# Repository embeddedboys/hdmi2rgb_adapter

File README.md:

HDMI2RGB Adapter
----------------

hdmi2rgb_adapter is a simple HDMI to RGB deserializer based on TFP401 (TI) 

FAQS
----

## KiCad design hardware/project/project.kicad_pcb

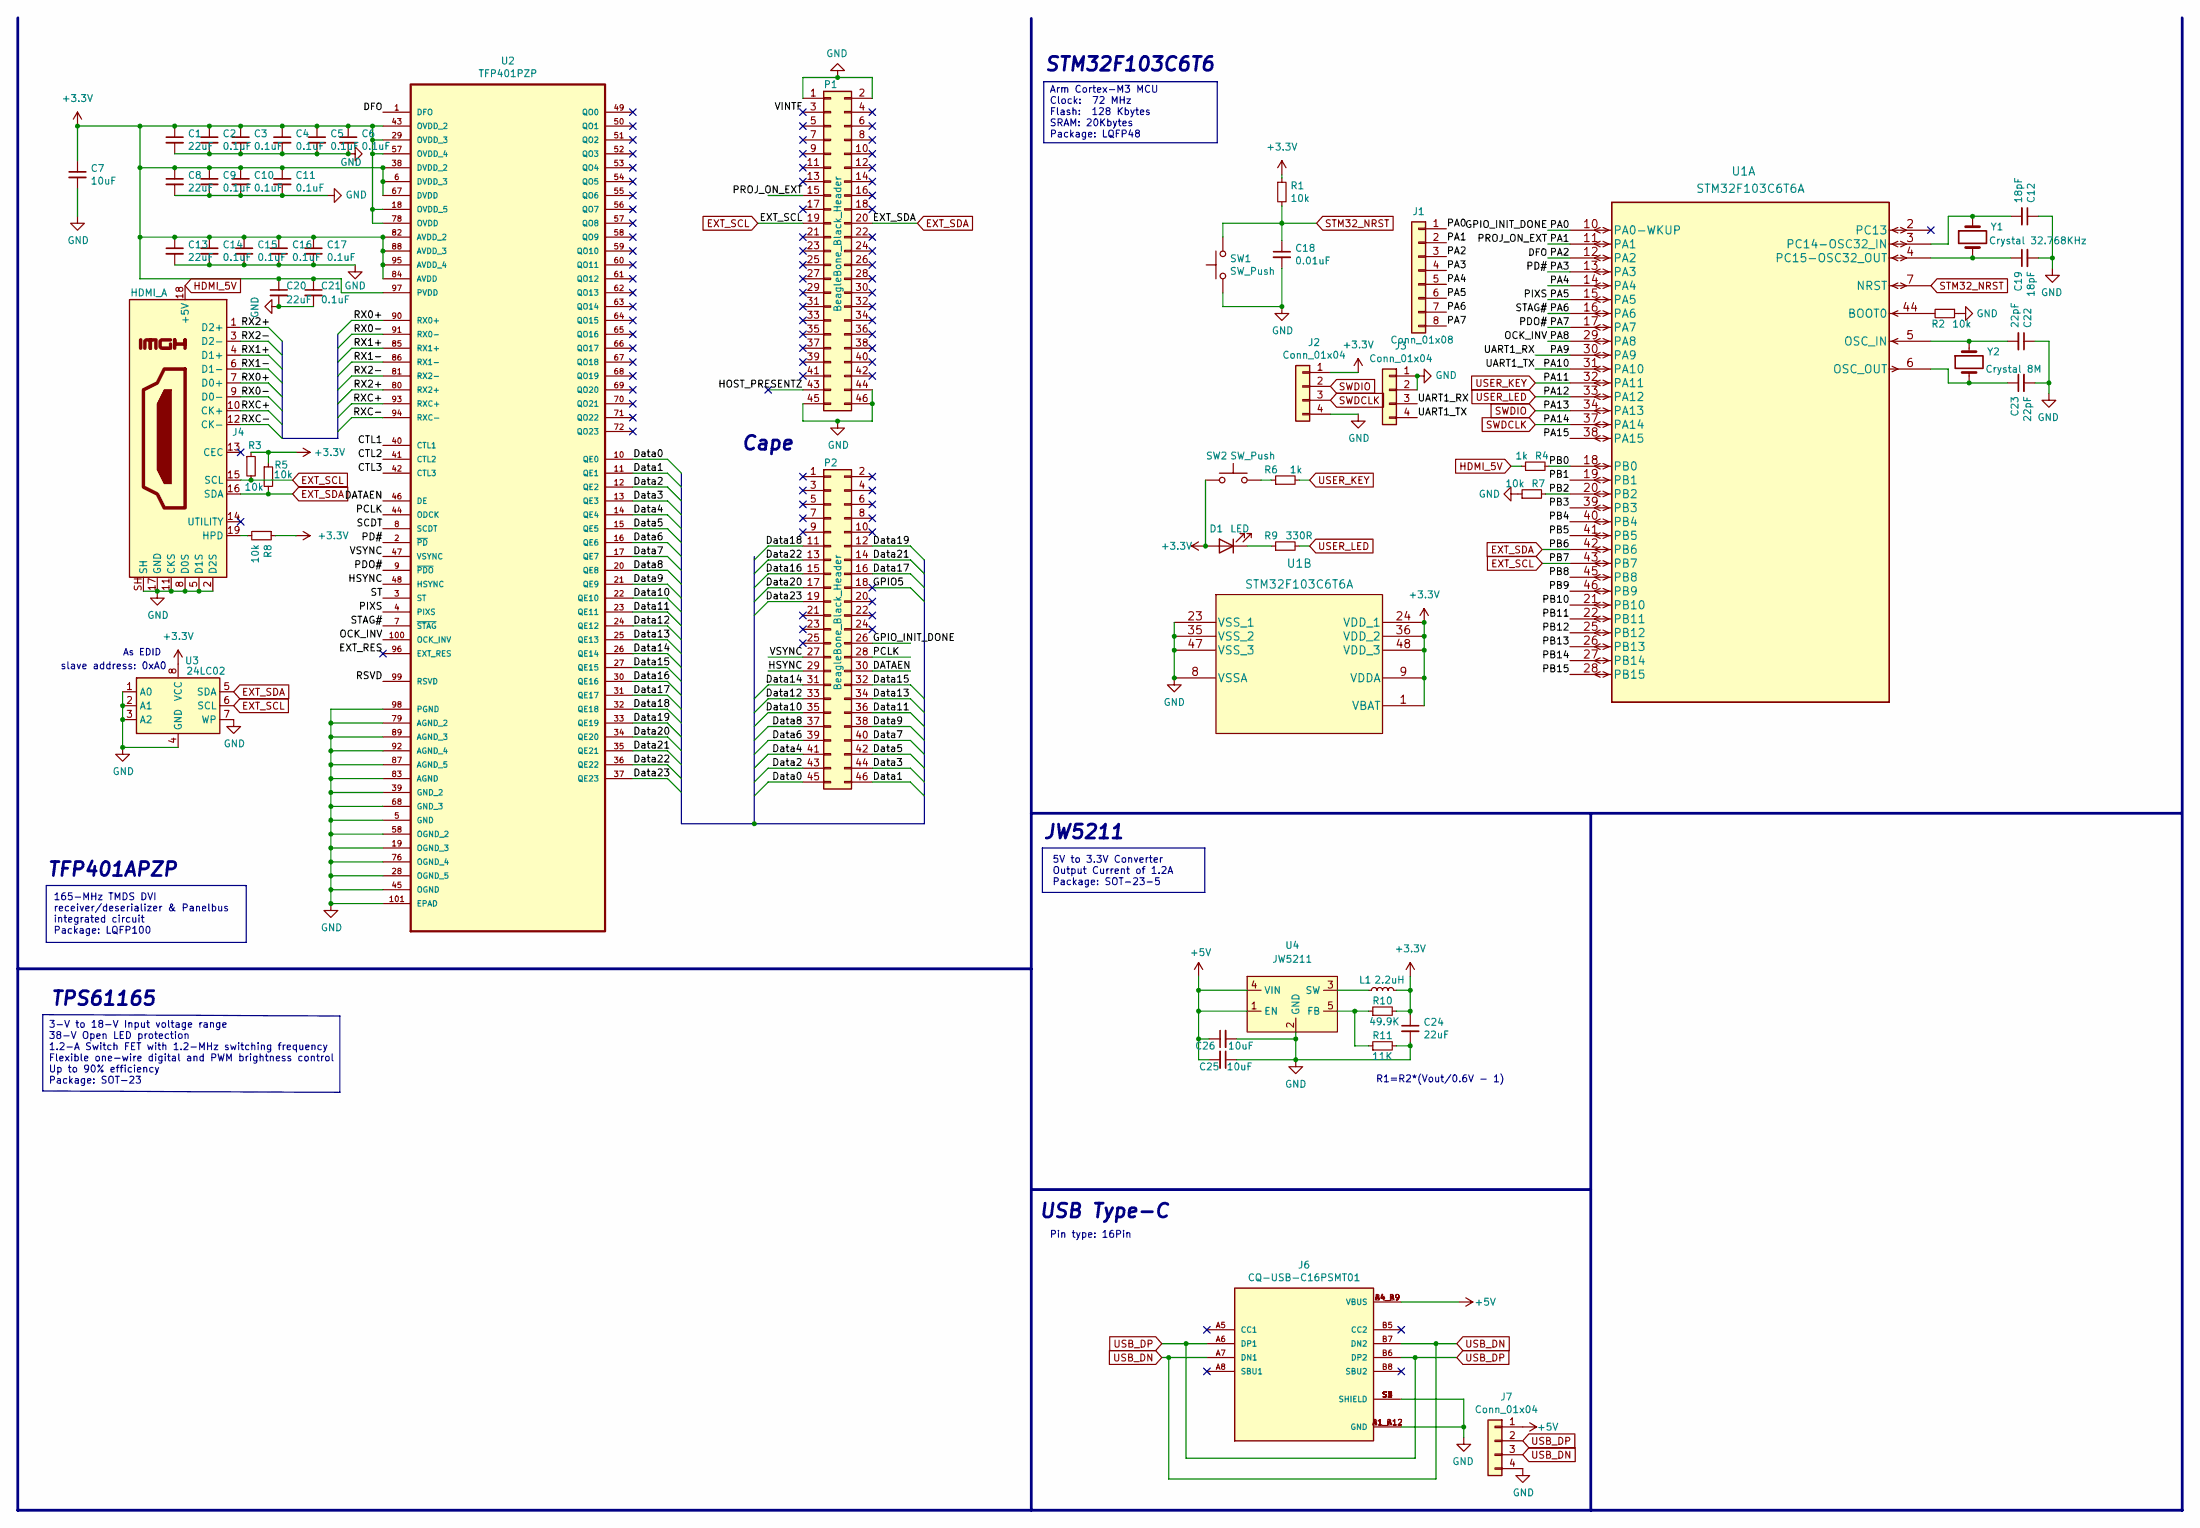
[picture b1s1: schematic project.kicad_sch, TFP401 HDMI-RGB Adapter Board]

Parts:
C1, C8, C13, C20, C24: 22uF; C_0805_2012Metric
C2, C3, C4, C5, C6, C9, C10, C11, C14, C15, C16, C17, C21: 0.1uF; C_0805_2012Metric
C7, C25, C26: 10uF; C_0805_2012Metric
C12, C19: 18pF; C_0805_2012Metric
C18: 0.01uF; C_0805_2012Metric
C22, C23: 22pF; C_0805_2012Metric
D1: LED; LED_0805_2012Metric
J1: Conn_01x08; PinHeader_1x08_P2.54mm_Vertical
J2, J3, J7: Conn_01x04; PinHeader_1x04_P2.54mm_Vertical
J4: HDMI_A; TE_1827059-3
J6: CQ-USB-C16PSMT01; SHENZHEN-CHUANGQIN-TECHNOLOGY_CQ-USB-C16PSMT01; PARTREV A
L1: 2.2uH; L_7.3x7.3_H4.5
P1, P2: BeagleBone_Black_Header; Socket_BeagleBone_Black
R1, R2, R3, R5, R7, R8: 10k; R_0805_2012Metric
R4, R6: 1k; R_0805_2012Metric
R9: 330R; R_0805_2012Metric
R10: 49.9K; R_0805_2012Metric
R11: 11K; R_0805_2012Metric
SW1, SW2: SW_Push; SW_SPST_CK_KXT3
U1: STM32F103C6T6A
U2: TFP401PZP; QFP50P1600X1600X120-101N; MPN TFP401PZP
U3: 24LC02; SOIC-8-1EP_3.9x4.9mm_P1.27mm_EP2.29x3mm
U4: JW5211; SOT-23-5
Y1: Crystal 32.768KHz; Crystal_SMD_3215-2Pin_3.2x1.5mm
Y2: Crystal 8M; Crystal_SMD_5032-2Pin_5.0x3.2mm

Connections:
+3V3: C1.1, C2.1, C3.1, C4.1, C5.1, C6.1, C7.1, C8.1, C9.1, C10.1, C11.1, C13.1, C14.1, C15.1, C16.1, C17.1, C20.1, C21.1, C24.1, D1.2 (A), J2.1, L1.2, R1.1, R3.1, R5.1, R8.1, R10.2, SW2.1, U1.1 (VBAT), U1.9 (VDDA), U1.24 (VDD_1), U1.36 (VDD_2), U1.48 (VDD_3), U2.6 (DVDD_3), U2.18 (OVDD_5), U2.29 (OVDD_3), U2.38 (DVDD_2), U2.43 (OVDD_2), U2.57 (OVDD_4), U2.67 (DVDD), U2.78 (OVDD), U2.82 (AVDD_2), U2.84 (AVDD), U2.88 (AVDD_3), U2.95 (AVDD_4), U2.97 (PVDD), U3.8 (VCC)
+5V: C25.2, C26.1, J6.A4_B9 (VBUS), J6.B4_A9 (VBUS), J7.1, U4.1 (EN), U4.4 (VIN)
/CTL1: U2.40 (CTL1)
/CTL2: U2.41 (CTL2)
/CTL3: U2.42 (CTL3)
/DATAEN: P2.30, U2.46 (DE)
/DFO: J1.3, U1.12 (PA2), U2.1 (DFO)
/Data0: P2.45, U2.10 (QE0)
/Data1: P2.46, U2.11 (QE1)
/Data2: P2.43, U2.12 (QE2)
/Data3: P2.44, U2.13 (QE3)
/Data4: P2.41, U2.14 (QE4)
/Data5: P2.42, U2.15 (QE5)
/Data6: P2.39, U2.16 (QE6)
/Data7: P2.40, U2.17 (QE7)
/Data8: P2.37, U2.20 (QE8)
/Data9: P2.38, U2.21 (QE9)
/Data10: P2.35, U2.22 (QE10)
/Data11: P2.36, U2.23 (QE11)
/Data12: P2.33, U2.24 (QE12)
/Data13: P2.34, U2.25 (QE13)
/Data14: P2.31, U2.26 (QE14)
/Data15: P2.32, U2.27 (QE15)
/Data16: P2.15, U2.30 (QE16)
/Data17: P2.16, U2.31 (QE17)
/Data18: P2.11, U2.32 (QE18)
/Data19: P2.12, U2.33 (QE19)
/Data20: P2.17, U2.34 (QE20)
/Data21: P2.14, U2.35 (QE21)
/Data22: P2.13, U2.36 (QE22)
/Data23: P2.19, U2.37 (QE23)
/EXT_RES: U2.96 (EXT_RES)
/GPIO5: P2.18
/GPIO_INIT_DONE: J1.1, P2.26, U1.10 (PA0-WKUP)
/HOST_PRESENTZ: P1.43
/HSYNC: P2.29, U2.48 (HSYNC)
/OCK_INV: U1.29 (PA8), U2.100 (OCK_INV)
/PA1: J1.2, P1.15, U1.11 (PA1)
/PA3: J1.4, U1.13 (PA3), U2.2 (~PD)
/PA4: J1.5, U1.14 (PA4)
/PA5: J1.6, U1.15 (PA5), U2.4 (PIXS)
/PA6: J1.7, U1.16 (PA6), U2.7 (~STAG)
/PA7: J1.8, U1.17 (PA7), U2.9 (~PDO)
/PA9: J3.3, U1.30 (PA9)
/PA10: J3.4, U1.31 (PA10)
/PA15: U1.38 (PA15)
/PB0: R4.2, U1.18 (PB0)
/PB1: U1.19 (PB1)
/PB2: R7.2, U1.20 (PB2)
/PB3: U1.39 (PB3)
/PB4: U1.40 (PB4)
/PB5: U1.41 (PB5)
/PB8: U1.45 (PB8)
/PB9: U1.46 (PB9)
/PB10: U1.21 (PB10)
/PB11: U1.22 (PB11)
/PB12: U1.25 (PB12)
/PB13: U1.26 (PB13)
/PB14: U1.27 (PB14)
/PB15: U1.28 (PB15)
/PCLK: P2.28, U2.44 (ODCK)
/RSVD: U2.99 (RSVD)
/RX0+: J4.7 (D0+), U2.90 (RX0+)
/RX0-: J4.9 (D0-), U2.91 (RX0-)
/RX1+: J4.4 (D1+), U2.85 (RX1+)
/RX1-: J4.6 (D1-), U2.86 (RX1-)
/RX2+: J4.1 (D2+), U2.80 (RX2+)
/RX2-: J4.3 (D2-), U2.81 (RX2-)
/RXC+: J4.10 (CK+), U2.93 (RXC+)
/RXC-: J4.12 (CK-), U2.94 (RXC-)
/SCDT: U2.8 (SCDT)
/ST: U2.3 (ST)
/VINTF: P1.3
/VSYNC: P2.27, U2.47 (VSYNC)
EXT_SCL: J4.15 (SCL), P1.19, R3.2, U1.43 (PB7), U3.6 (SCL)
EXT_SDA: J4.16 (SDA), P1.20, R5.2, U1.42 (PB6), U3.5 (SDA)
GND: C1.2, C2.2, C3.2, C4.2, C5.2, C6.2, C7.2, C8.2, C9.2, C10.2, C11.2, C12.1, C13.2, C14.2, C15.2, C16.2, C17.2, C18.2, C19.2, C20.2, C21.2, C22.1, C23.2, C24.2, C25.1, C26.2, J2.4, J3.1, J3.2, J4.2 (D2S), J4.5 (D1S), J4.8 (D0S), J4.11 (CKS), J4.17 (GND), J4.SH, J6.A1_B12 (GND), J6.B1_A12 (GND), J6.S1 (SHIELD), J6.S2 (SHIELD), J6.S3 (SHIELD), J6.S4 (SHIELD), J7.4, P1.1, P1.2, P1.44, P1.45, P1.46, R2.1, R7.1, R11.2, SW1.1, U1.8 (VSSA), U1.23 (VSS_1), U1.35 (VSS_2), U1.47 (VSS_3), U2.5 (GND), U2.19 (OGND_3), U2.28 (OGND_5), U2.39 (GND_2), U2.45 (OGND), U2.58 (OGND_2), U2.68 (GND_3), U2.76 (OGND_4), U2.79 (AGND_2), U2.83 (AGND), U2.87 (AGND_5), U2.89 (AGND_3), U2.92 (AGND_4), U2.98 (PGND), U2.101 (EPAD), U3.1 (A0), U3.2 (A1), U3.3 (A2), U3.4 (GND), U3.7 (WP), U4.2 (GND)
HDMI_5V: J4.18 (+5V), R4.1
unnamed: C12.2, U1.3 (PC14-OSC32_IN), Y1.1
unnamed: C19.1, U1.4 (PC15-OSC32_OUT), Y1.2
unnamed: C22.2, U1.5 (OSC_IN), Y2.1
unnamed: C23.1, U1.6 (OSC_OUT), Y2.2
unnamed: D1.1 (K), R9.1
unnamed: J4.19 (HPD), R8.2
unnamed: L1.1, U4.3 (SW)
unnamed: R2.2, U1.44 (BOOT0)
unnamed: R6.1, SW2.2
unnamed: R10.1, R11.1, U4.5 (FB)
STM32_NRST: C18.1, R1.2, SW1.2, U1.7 (NRST)
SWDCLK: J2.3, U1.37 (PA14)
SWDIO: J2.2, U1.34 (PA13)
USB_DN: J6.A7 (DN1), J6.B7 (DN2), J7.3
USB_DP: J6.A6 (DP1), J6.B6 (DP2), J7.2
USER_KEY: R6.2, U1.32 (PA11)
USER_LED: R9.2, U1.33 (PA12)

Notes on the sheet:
R1=R2*(Vout/0.6V - 1)
JW5211
165-MHz TMDS DVI receiver/deserializer & Panelbus integrated circuit Package: LQFP100
slave address: 0xA0
5V to 3.3V Converter Output Current of 1.2A Package: SOT-23-5
Cape
USB Type-C
Arm Cortex-M3 MCU Clock: 72 MHz Flash: 128 Kbytes SRAM: 20Kbytes Package: LQFP48
Pin type: 16Pin
TPS61165
STM32F103C6T6
As EDID
3-V to 18-V Input voltage range 38-V Open LED protection 1.2-A Switch FET with 1.2-MHz switching frequency Flexible one-wire digital and PWM brightness control Up to 90% efficiency Package: SOT-23
TFP401APZP

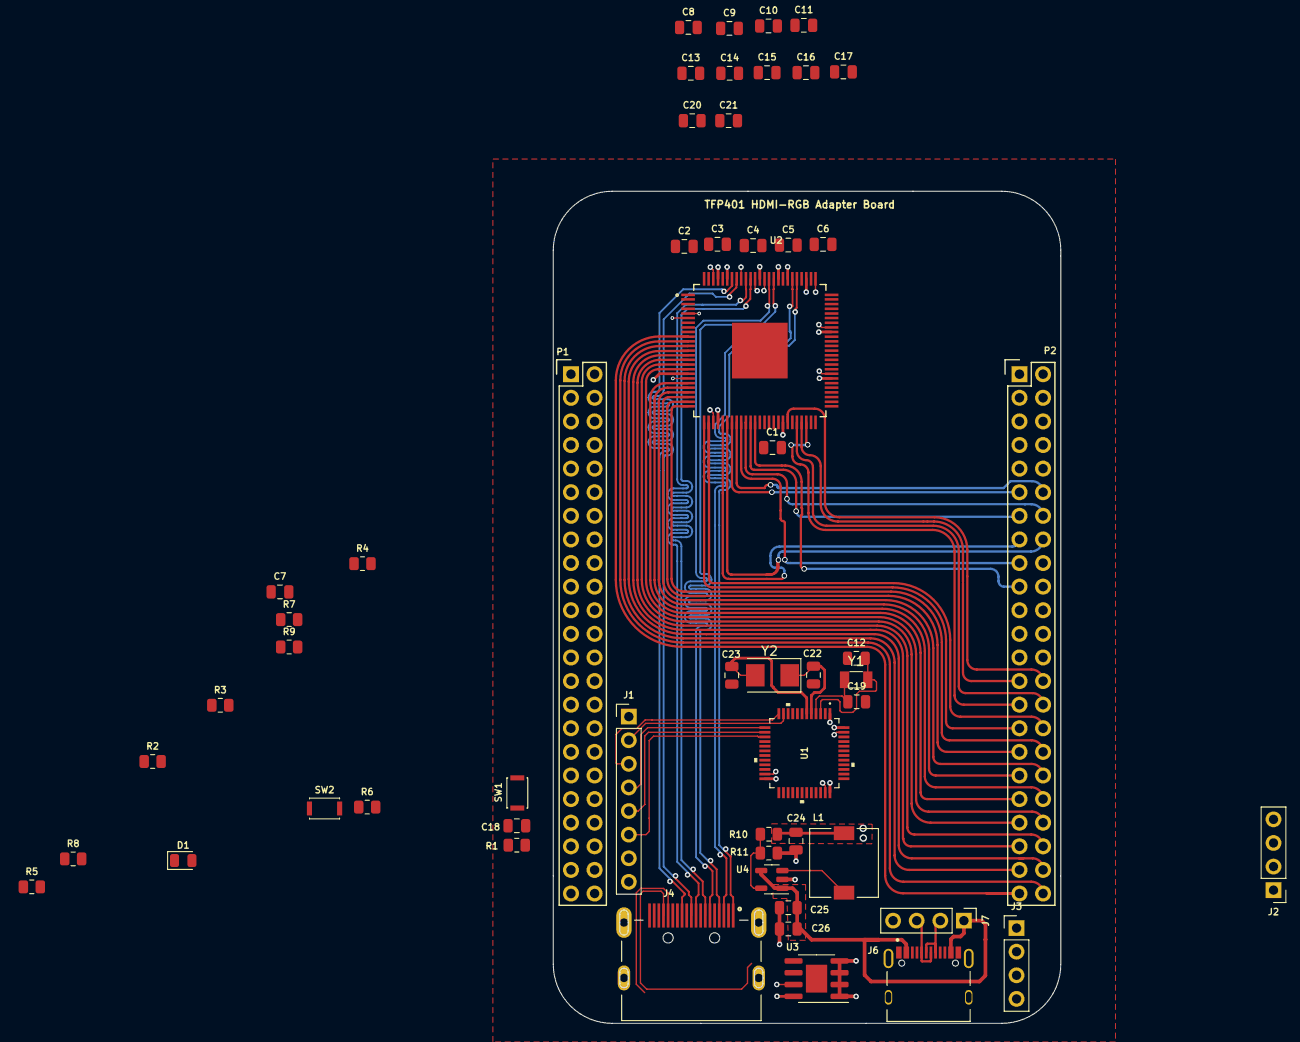
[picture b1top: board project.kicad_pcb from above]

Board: 4 copper layers, 54.6 x 89.5 mm, 55 parts (0 on the bottom side), 72 nets.

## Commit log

2022-02-05 add license.
2022-02-05 add .gitignore
2022-02-05 add README
2022-02-05 add Documentation which based on mkdocs
2022-02-05 Add the first batch of datasheets
2022-02-05 add references
2022-02-05 add hardware
